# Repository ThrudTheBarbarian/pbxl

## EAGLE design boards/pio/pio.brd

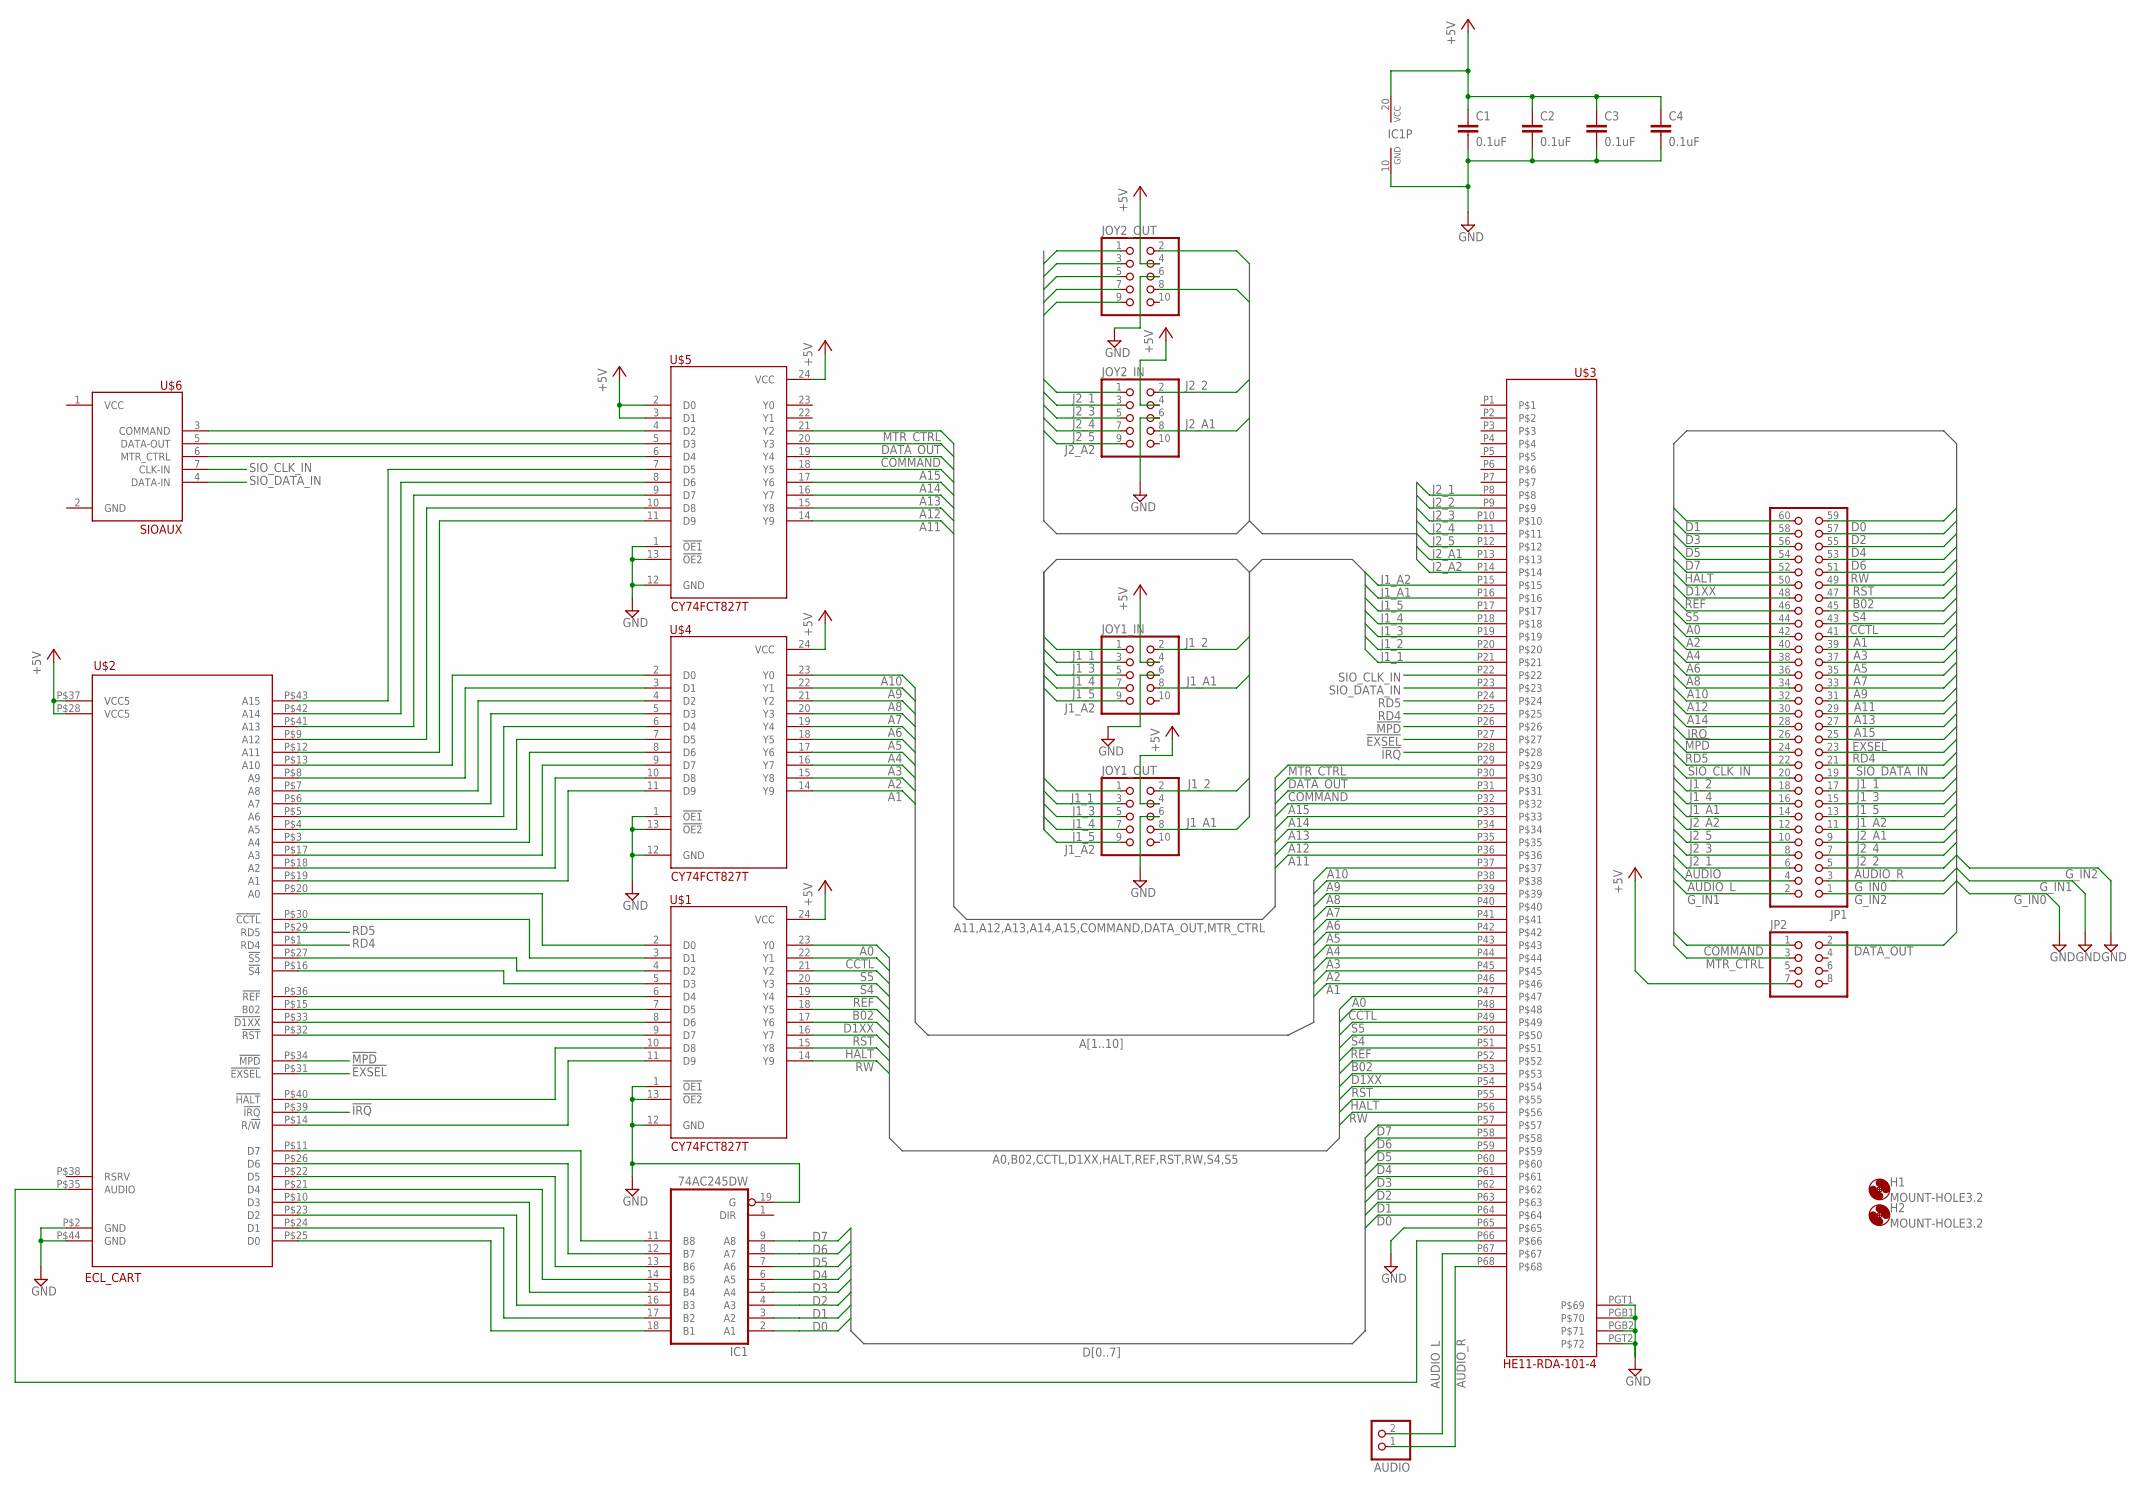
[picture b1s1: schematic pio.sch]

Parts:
AUDIO: PINHD-1X2; 1X02
C1, C2, C3, C4: 0.1uF; C1206
H1, H2: MOUNT-HOLE3.2; 3,2
IC1: 74AC245DW; SO20W
JOY1_IN, JOY1_OUT, JOY2_IN, JOY2_OUT: PINHD-2X5; 2X05
JP1: PINHD-2X30; 2X30
JP2: PINHD-2X4; 2X04
U$1, U$4, U$5: CY74FCT827T; SO24L
U$2: ECL_CART
U$3: HE11-RDA-101-4
U$6: SIOAUX; 1X07

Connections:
!EXSEL!: JP1.25, U$2.P$31 (!EXSEL!), U$3.P27
!IRQ!: JP1.28, U$2.P$39 (!IRQ!), U$3.P28
!MPD!: JP1.26, U$2.P$34 (!MPD!), U$3.P26
+5V: C1.1, C2.1, C3.1, C4.1, IC1.20 (VCC), JOY1_IN.4, JOY1_OUT.4, JOY2_IN.4, JOY2_OUT.4, JP2.7, U$1.24 (VCC), U$2.P$28 (VCC5), U$2.P$37 (VCC5), U$4.24 (VCC), U$5.2 (D0), U$5.3 (D1), U$5.24 (VCC)
A0: JP1.44, U$1.23 (Y0), U$3.P47
A1: JP1.41, U$3.P46, U$4.14 (Y9)
A2: JP1.42, U$3.P45, U$4.15 (Y8)
A3: JP1.39, U$3.P44, U$4.16 (Y7)
A4: JP1.40, U$3.P43, U$4.17 (Y6)
A5: JP1.37, U$3.P42, U$4.18 (Y5)
A6: JP1.38, U$3.P41, U$4.19 (Y4)
A7: JP1.35, U$3.P40, U$4.20 (Y3)
A8: JP1.36, U$3.P39, U$4.21 (Y2)
A9: JP1.33, U$3.P38, U$4.22 (Y1)
A10: JP1.34, U$3.P37, U$4.23 (Y0)
A11: JP1.31, U$3.P36, U$5.14 (Y9)
A12: JP1.32, U$3.P35, U$5.15 (Y8)
A13: JP1.29, U$3.P34, U$5.16 (Y7)
A14: JP1.30, U$3.P33, U$5.17 (Y6)
A15: JP1.27, U$3.P32, U$5.18 (Y5)
AUDIO: JP1.6, U$2.P$35 (AUDIO), U$3.P66
AUDIO_L: AUDIO.2, JP1.4, U$3.P67
AUDIO_R: AUDIO.1, JP1.5, U$3.P68
B02: JP1.47, U$1.18 (Y5), U$3.P52
CCTL: JP1.43, U$1.22 (Y1), U$3.P48
COMMAND: JP2.1, U$3.P31, U$5.19 (Y4)
D0: IC1.2 (A1), JP1.59, U$3.P64
D1: IC1.3 (A2), JP1.60, U$3.P63
D1XX: JP1.50, U$1.17 (Y6), U$3.P53
D2: IC1.4 (A3), JP1.57, U$3.P62
D3: IC1.5 (A4), JP1.58, U$3.P61
D4: IC1.6 (A5), JP1.55, U$3.P60
D5: IC1.7 (A6), JP1.56, U$3.P59
D6: IC1.8 (A7), JP1.53, U$3.P58
D7: IC1.9 (A8), JP1.54, U$3.P57
DATA_OUT: JP2.2, U$3.P30, U$5.20 (Y3)
GND: C1.2, C2.2, C3.2, C4.2, IC1.10 (GND), IC1.19 (G), JOY1_IN.6, JOY1_OUT.6, JOY2_IN.6, JOY2_OUT.6, U$1.1 (!OE1!), U$1.12 (GND), U$1.13 (!OE2!), U$2.P$2 (GND), U$2.P$44 (GND), U$3.P65, U$3.PGB1, U$3.PGB2, U$3.PGT1, U$3.PGT2, U$4.1 (!OE1!), U$4.12 (GND), U$4.13 (!OE2!), U$5.1 (!OE1!), U$5.12 (GND), U$5.13 (!OE2!)
G_IN0: JP1.3
G_IN1: JP1.2
G_IN2: JP1.1
HALT: JP1.52, U$1.15 (Y8), U$3.P55
J1_1: JOY1_IN.1, JOY1_OUT.1, JP1.19, U$3.P21
J1_2: JOY1_IN.2, JOY1_OUT.2, JP1.20, U$3.P20
J1_3: JOY1_IN.3, JOY1_OUT.3, JP1.17, U$3.P19
J1_4: JOY1_IN.5, JOY1_OUT.5, JP1.18, U$3.P18
J1_5: JOY1_IN.7, JOY1_OUT.7, JP1.15, U$3.P17
J1_A1: JOY1_IN.8, JOY1_OUT.8, JP1.16, U$3.P16
J1_A2: JOY1_IN.9, JOY1_OUT.9, JP1.13, U$3.P15
J2_1: JOY2_IN.1, JOY2_OUT.1, JP1.8, U$3.P8
J2_2: JOY2_IN.2, JOY2_OUT.2, JP1.7, U$3.P9
J2_3: JOY2_IN.3, JOY2_OUT.3, JP1.10, U$3.P10
J2_4: JOY2_IN.5, JOY2_OUT.5, JP1.9, U$3.P11
J2_5: JOY2_IN.7, JOY2_OUT.7, JP1.12, U$3.P12
J2_A1: JOY2_IN.8, JOY2_OUT.8, JP1.11, U$3.P13
J2_A2: JOY2_IN.9, JOY2_OUT.9, JP1.14, U$3.P14
MTR_CTRL: JP2.3, U$3.P29, U$5.21 (Y2)
unnamed: U$1.11 (D9), U$2.P$14 (R/!W!)
unnamed: U$1.10 (D8), U$2.P$40 (!HALT!)
unnamed: U$1.9 (D7), U$2.P$32 (!RST!)
unnamed: U$1.8 (D6), U$2.P$33 (!D1XX!)
unnamed: U$1.7 (D5), U$2.P$15 (B02)
unnamed: U$1.6 (D4), U$2.P$36 (!REF!)
unnamed: U$1.5 (D3), U$2.P$16 (!S4!)
unnamed: U$1.4 (D2), U$2.P$27 (!S5!)
unnamed: U$1.3 (D1), U$2.P$30 (!CCTL!)
unnamed: U$1.2 (D0), U$2.P$20 (A0)
unnamed: U$2.P$19 (A1), U$4.11 (D9)
unnamed: U$2.P$18 (A2), U$4.10 (D8)
unnamed: U$2.P$17 (A3), U$4.9 (D7)
unnamed: U$2.P$3 (A4), U$4.8 (D6)
unnamed: U$2.P$4 (A5), U$4.7 (D5)
unnamed: U$2.P$5 (A6), U$4.6 (D4)
unnamed: U$2.P$6 (A7), U$4.5 (D3)
unnamed: U$2.P$7 (A8), U$4.4 (D2)
unnamed: U$2.P$8 (A9), U$4.3 (D1)
unnamed: U$2.P$13 (A10), U$4.2 (D0)
unnamed: U$5.6 (D4), U$6.6 (MTR_CTRL)
unnamed: U$5.5 (D3), U$6.5 (DATA-OUT)
unnamed: U$5.4 (D2), U$6.3 (COMMAND)
unnamed: U$2.P$12 (A11), U$5.11 (D9)
unnamed: U$2.P$9 (A12), U$5.10 (D8)
unnamed: U$2.P$41 (A13), U$5.9 (D7)
unnamed: U$2.P$42 (A14), U$5.8 (D6)
unnamed: U$2.P$43 (A15), U$5.7 (D5)
unnamed: IC1.11 (B8), U$2.P$11 (D7)
unnamed: IC1.12 (B7), U$2.P$26 (D6)
unnamed: IC1.13 (B6), U$2.P$22 (D5)
unnamed: IC1.14 (B5), U$2.P$21 (D4)
unnamed: IC1.15 (B4), U$2.P$10 (D3)
unnamed: IC1.16 (B3), U$2.P$23 (D2)
unnamed: IC1.17 (B2), U$2.P$24 (D1)
unnamed: IC1.18 (B1), U$2.P$25 (D0)
RD4: JP1.23, U$2.P$1 (RD4), U$3.P25
RD5: JP1.24, U$2.P$29 (RD5), U$3.P24
REF: JP1.48, U$1.19 (Y4), U$3.P51
RST: JP1.49, U$1.16 (Y7), U$3.P54
RW: JP1.51, U$1.14 (Y9), U$3.P56
S4: JP1.45, U$1.20 (Y3), U$3.P50
S5: JP1.46, U$1.21 (Y2), U$3.P49
SIO_CLK_IN: JP1.22, U$3.P22, U$6.7 (CLK-IN)
SIO_DATA_IN: JP1.21, U$3.P23, U$6.4 (DATA-IN)

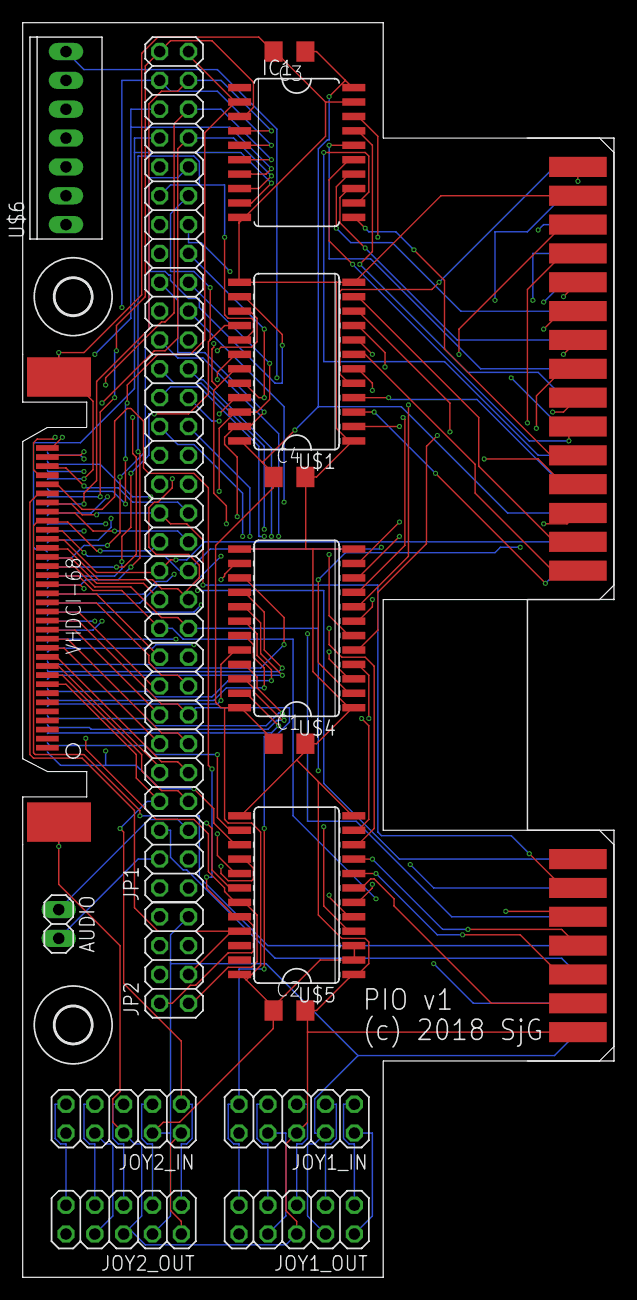
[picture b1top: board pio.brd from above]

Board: 4 copper layers, 52.1 x 110.5 mm, 20 parts (0 on the bottom side), 98 nets.

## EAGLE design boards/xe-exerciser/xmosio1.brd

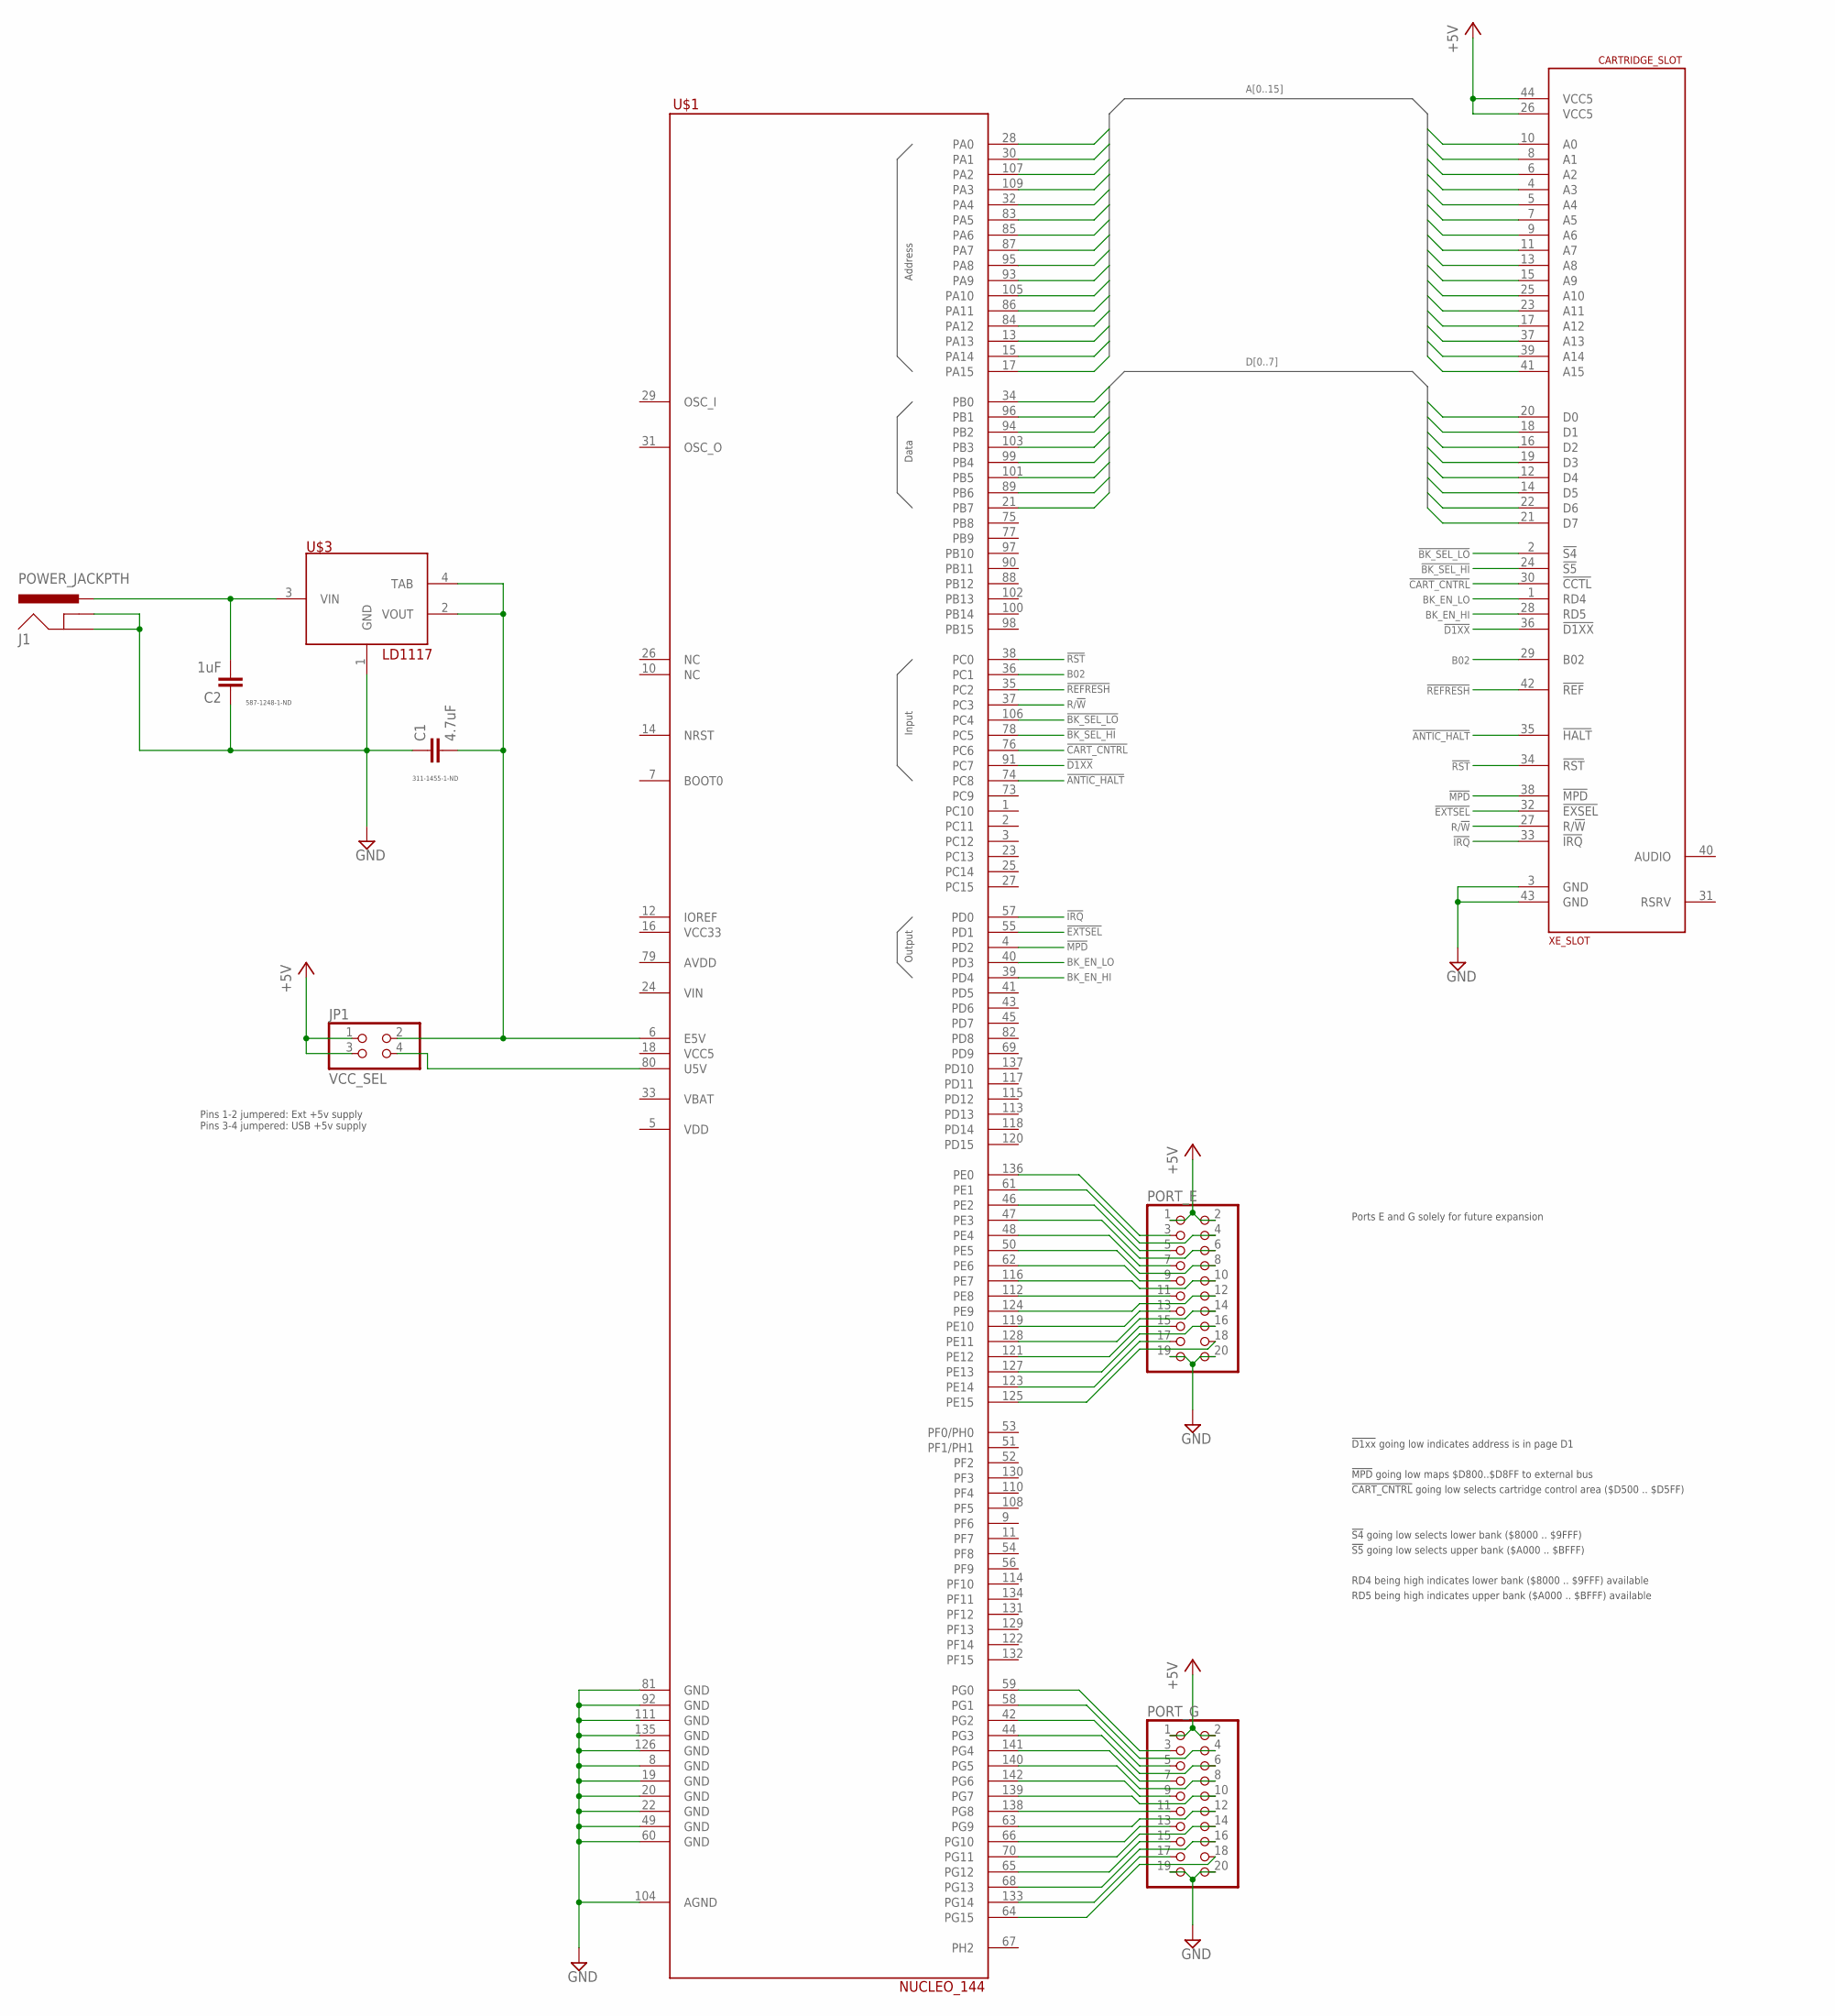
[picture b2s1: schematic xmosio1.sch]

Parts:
C1: 4.7uF; C0603
C2: 1uF; C0603
CARTRIDGE_SLOT: XE_SLOT
J1: POWER_JACKPTH; POWER_JACK_PTH
JP1: VCC_SEL; 2X02
PORT_E: PINHD-2X10; 2X10
PORT_G: PINHD-2X10; 2X10
U$1: NUCLEO_144
U$3: LD1117; SOT223

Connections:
!ANTIC_HALT!: CARTRIDGE_SLOT.35 (!HALT!), U$1.74 (PC8)
!BK_SEL_HI!: CARTRIDGE_SLOT.24 (!S5!), U$1.78 (PC5)
!BK_SEL_LO!: CARTRIDGE_SLOT.2 (!S4!), U$1.106 (PC4)
!CART_CNTRL!: CARTRIDGE_SLOT.30 (!CCTL!), U$1.76 (PC6)
!D1XX!: CARTRIDGE_SLOT.36 (!D1XX!), U$1.91 (PC7)
!EXTSEL!: CARTRIDGE_SLOT.32 (!EXSEL!), U$1.55 (PD1)
!IRQ!: CARTRIDGE_SLOT.33 (!IRQ!), U$1.57 (PD0)
!MPD!: CARTRIDGE_SLOT.38 (!MPD!), U$1.4 (PD2)
!REFRESH!: CARTRIDGE_SLOT.42 (!REF!), U$1.35 (PC2)
!RST!: CARTRIDGE_SLOT.34 (!RST!), U$1.38 (PC0)
+5V: CARTRIDGE_SLOT.26 (VCC5), CARTRIDGE_SLOT.44 (VCC5), JP1.1, JP1.3, PORT_E.1, PORT_E.2, PORT_G.1, PORT_G.2
A0: CARTRIDGE_SLOT.10 (A0), U$1.28 (PA0)
A1: CARTRIDGE_SLOT.8 (A1), U$1.30 (PA1)
A2: CARTRIDGE_SLOT.6 (A2), U$1.107 (PA2)
A3: CARTRIDGE_SLOT.4 (A3), U$1.109 (PA3)
A4: CARTRIDGE_SLOT.5 (A4), U$1.32 (PA4)
A5: CARTRIDGE_SLOT.7 (A5), U$1.83 (PA5)
A6: CARTRIDGE_SLOT.9 (A6), U$1.85 (PA6)
A7: CARTRIDGE_SLOT.11 (A7), U$1.87 (PA7)
A8: CARTRIDGE_SLOT.13 (A8), U$1.95 (PA8)
A9: CARTRIDGE_SLOT.15 (A9), U$1.93 (PA9)
A10: CARTRIDGE_SLOT.25 (A10), U$1.105 (PA10)
A11: CARTRIDGE_SLOT.23 (A11), U$1.86 (PA11)
A12: CARTRIDGE_SLOT.17 (A12), U$1.84 (PA12)
A13: CARTRIDGE_SLOT.37 (A13), U$1.13 (PA13)
A14: CARTRIDGE_SLOT.39 (A14), U$1.15 (PA14)
A15: CARTRIDGE_SLOT.41 (A15), U$1.17 (PA15)
B02: CARTRIDGE_SLOT.29 (B02), U$1.36 (PC1)
BK_EN_HI: CARTRIDGE_SLOT.28 (RD5), U$1.39 (PD4)
BK_EN_LO: CARTRIDGE_SLOT.1 (RD4), U$1.40 (PD3)
D0: CARTRIDGE_SLOT.20 (D0), U$1.34 (PB0)
D1: CARTRIDGE_SLOT.18 (D1), U$1.96 (PB1)
D2: CARTRIDGE_SLOT.16 (D2), U$1.94 (PB2)
D3: CARTRIDGE_SLOT.19 (D3), U$1.103 (PB3)
D4: CARTRIDGE_SLOT.12 (D4), U$1.99 (PB4)
D5: CARTRIDGE_SLOT.14 (D5), U$1.101 (PB5)
D6: CARTRIDGE_SLOT.22 (D6), U$1.89 (PB6)
D7: CARTRIDGE_SLOT.21 (D7), U$1.21 (PB7)
GND: C1.1, C2.1, CARTRIDGE_SLOT.3 (GND), CARTRIDGE_SLOT.43 (GND), J1.GND, J1.GNDBREAK, PORT_E.19, PORT_E.20, PORT_G.19, PORT_G.20, U$1.8 (GND), U$1.19 (GND), U$1.20 (GND), U$1.22 (GND), U$1.49 (GND), U$1.60 (GND), U$1.81 (GND), U$1.92 (GND), U$1.104 (AGND), U$1.111 (GND), U$1.126 (GND), U$1.135 (GND), U$3.1 (GND)
unnamed: C1.2, JP1.2, U$1.6 (E5V), U$3.2 (VOUT), U$3.4 (TAB)
unnamed: JP1.4, U$1.80 (U5V)
unnamed: PORT_E.3, U$1.136 (PE0)
unnamed: PORT_E.4, U$1.61 (PE1)
unnamed: PORT_E.5, U$1.46 (PE2)
unnamed: PORT_E.6, U$1.47 (PE3)
unnamed: PORT_E.7, U$1.48 (PE4)
unnamed: PORT_E.8, U$1.50 (PE5)
unnamed: PORT_E.9, U$1.62 (PE6)
unnamed: PORT_E.10, U$1.116 (PE7)
unnamed: PORT_E.11, U$1.112 (PE8)
unnamed: PORT_E.12, U$1.124 (PE9)
unnamed: PORT_E.13, U$1.119 (PE10)
unnamed: PORT_E.14, U$1.128 (PE11)
unnamed: PORT_E.15, U$1.121 (PE12)
unnamed: PORT_E.16, U$1.127 (PE13)
unnamed: PORT_E.17, U$1.123 (PE14)
unnamed: PORT_E.18, U$1.125 (PE15)
unnamed: PORT_G.3, U$1.59 (PG0)
unnamed: PORT_G.4, U$1.58 (PG1)
unnamed: PORT_G.5, U$1.42 (PG2)
unnamed: PORT_G.6, U$1.44 (PG3)
unnamed: PORT_G.7, U$1.141 (PG4)
unnamed: PORT_G.8, U$1.140 (PG5)
unnamed: PORT_G.9, U$1.142 (PG6)
unnamed: PORT_G.11, U$1.138 (PG8)
unnamed: C2.2, J1.PWR, U$3.3 (VIN)
unnamed: PORT_G.12, U$1.63 (PG9)
unnamed: PORT_G.13, U$1.66 (PG10)
unnamed: PORT_G.14, U$1.70 (PG11)
unnamed: PORT_G.15, U$1.65 (PG12)
unnamed: PORT_G.16, U$1.68 (PG13)
unnamed: PORT_G.17, U$1.133 (PG14)
unnamed: PORT_G.18, U$1.64 (PG15)
PORT_G: PORT_G.10, U$1.139 (PG7)
R/!W!: CARTRIDGE_SLOT.27 (R/!W!), U$1.37 (PC3)

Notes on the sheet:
!MPD! going low maps $D800..$D8FF to external bus
!S4! going low selects lower bank ($8000 .. $9FFF)
!S5! going low selects upper bank ($A000 .. $BFFF)
!CART_CNTRL! going low selects cartridge control area ($D500 .. $D5FF)
!D1xx! going low indicates address is in page D1
RD4 being high indicates lower bank ($8000 .. $9FFF) available
RD5 being high indicates upper bank ($A000 .. $BFFF) available
Output
Input
Data
Address
Pins 1-2 jumpered: Ext +5v supply Pins 3-4 jumpered: USB +5v supply
Ports E and G solely for future expansion
311-1455-1-ND
587-1248-1-ND

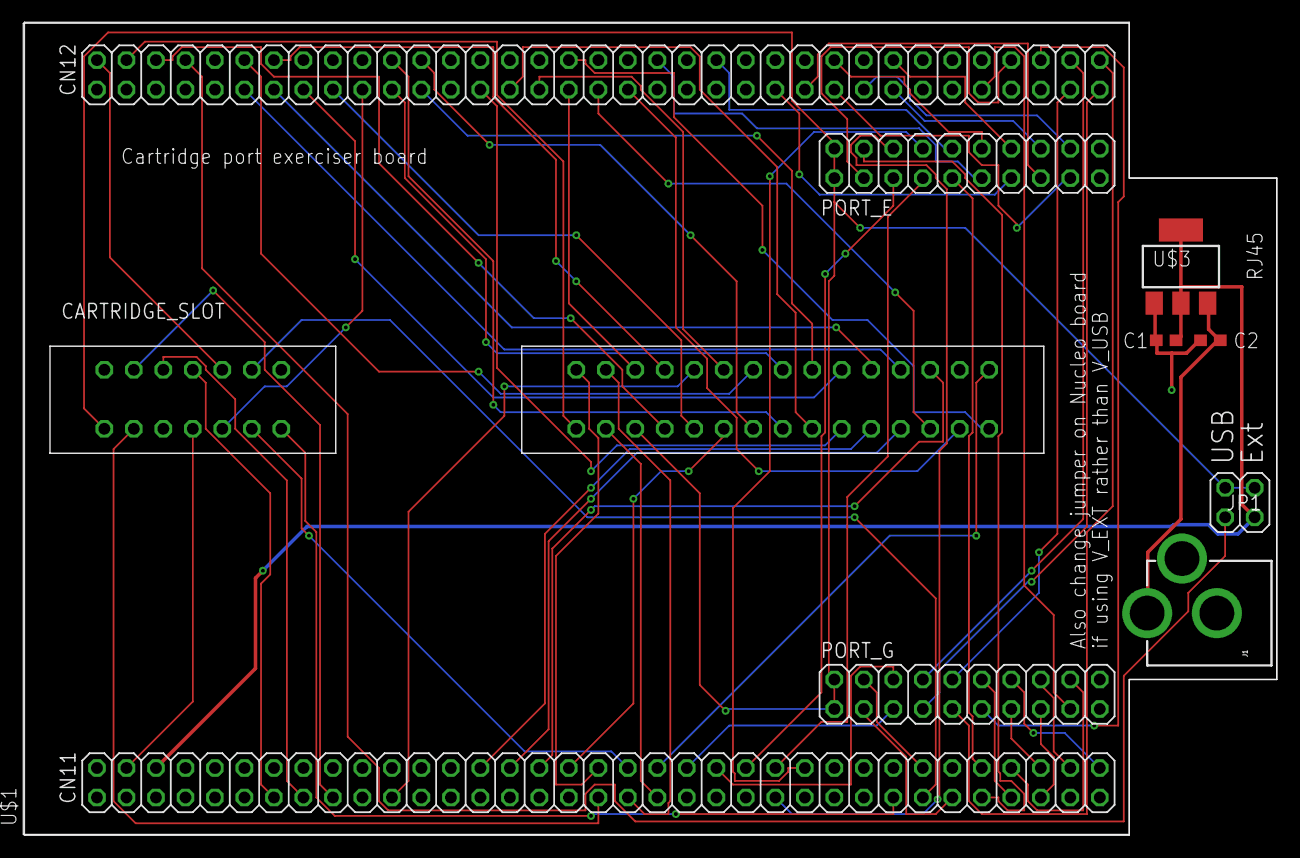
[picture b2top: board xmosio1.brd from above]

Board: 2 copper layers, 108.0 x 69.8 mm, 9 parts (0 on the bottom side), 75 nets.

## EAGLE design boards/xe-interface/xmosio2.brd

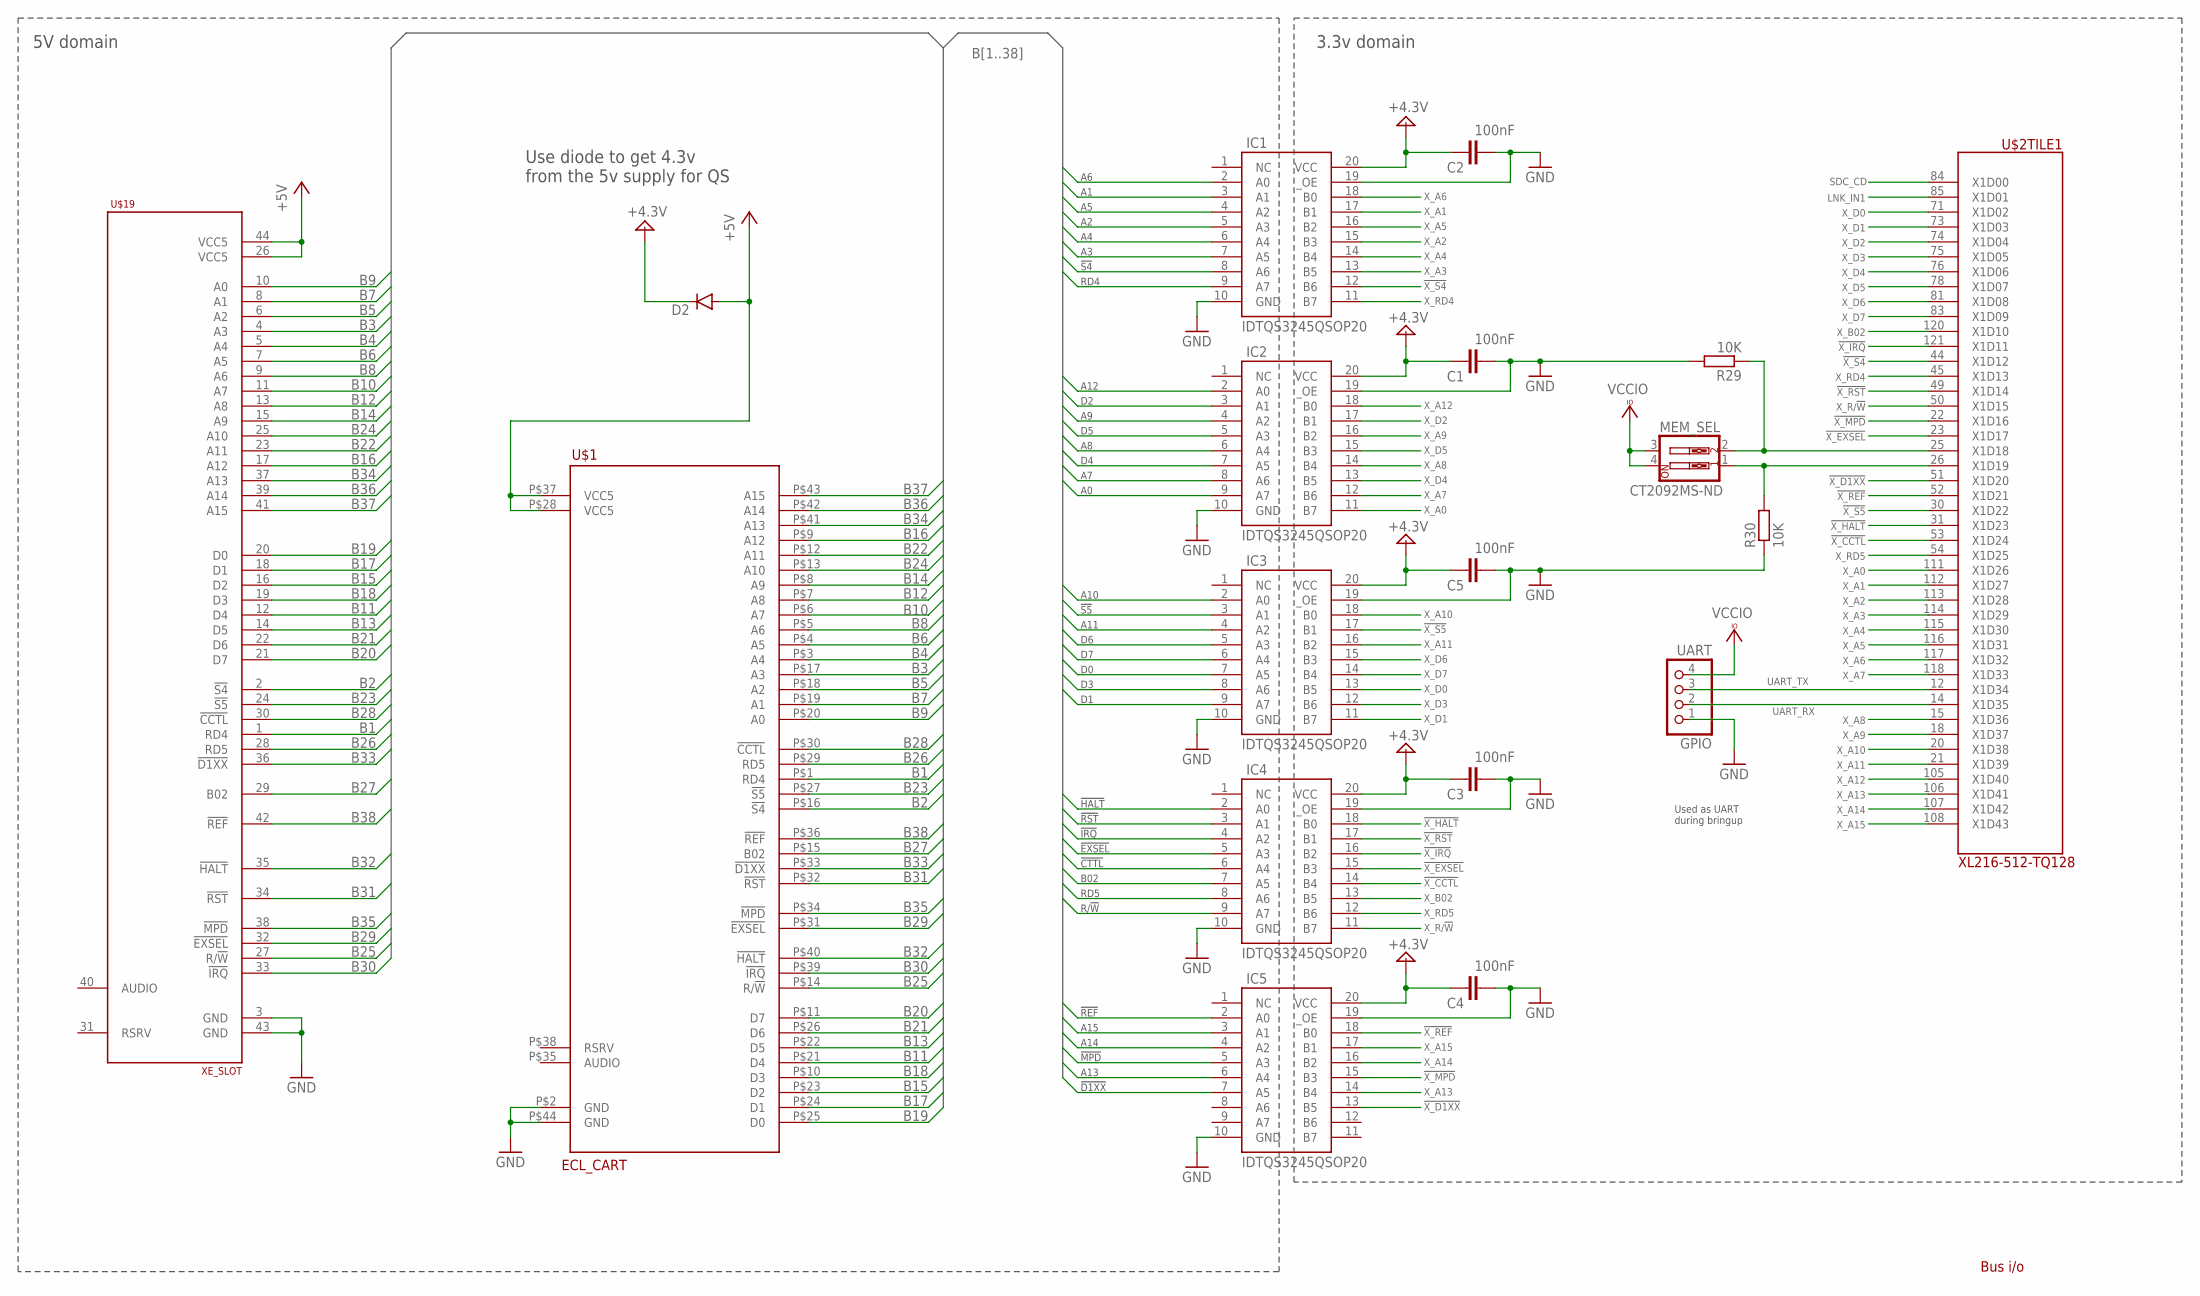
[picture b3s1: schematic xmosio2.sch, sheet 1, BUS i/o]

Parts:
C1, C2, C3, C4, C5: 100nF; C1206
D2: DIODE; DIODE-1N4001-KIT
GPIO: UART; 1X04
IC1, IC2, IC3, IC4, IC5: IDTQS3245QSOP20; QSOP20
MEM_SEL: CT2092MS-ND; EDG-02
R29, R30: 10K; R1206
U$1: ECL_CART
U$2: XL216-512-TQ128; TQFP128
U$19: XE_SLOT

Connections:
!X_CCTL!: IC4.14 (B4), U$2.53 (X1D24)
!X_D1XX!: IC5.13 (B5), U$2.51 (X1D20)
!X_EXSEL!: IC4.15 (B3), U$2.23 (X1D17)
!X_HALT!: IC4.18 (B0), U$2.31 (X1D23)
!X_IRQ!: IC4.16 (B2), U$2.121 (X1D11)
!X_MPD!: IC5.15 (B3), U$2.22 (X1D16)
!X_REF!: IC5.18 (B0), U$2.52 (X1D21)
!X_RST!: IC4.17 (B1), U$2.49 (X1D14)
!X_S4!: IC1.12 (B6), U$2.44 (X1D12)
!X_S5!: IC3.17 (B1), U$2.30 (X1D22)
+4.3V: C1.1, C2.1, C3.1, C4.1, C5.1, D2.C, IC1.20 (VCC), IC2.20 (VCC), IC3.20 (VCC), IC4.20 (VCC), IC5.20 (VCC)
+5V: D2.A, U$1.P$28 (VCC5), U$1.P$37 (VCC5), U$19.26 (VCC5), U$19.44 (VCC5); also elsewhere on the board
B1: IC1.9 (A7), U$1.P$1 (RD4), U$19.1 (RD4)
B2: IC1.8 (A6), U$1.P$16 (!S4!), U$19.2 (!S4!)
B3: IC1.7 (A5), U$1.P$17 (A3), U$19.4 (A3)
B4: IC1.6 (A4), U$1.P$3 (A4), U$19.5 (A4)
B5: IC1.5 (A3), U$1.P$18 (A2), U$19.6 (A2)
B6: IC1.4 (A2), U$1.P$4 (A5), U$19.7 (A5)
B7: IC1.3 (A1), U$1.P$19 (A1), U$19.8 (A1)
B8: IC1.2 (A0), U$1.P$5 (A6), U$19.9 (A6)
B9: IC2.9 (A7), U$1.P$20 (A0), U$19.10 (A0)
B10: IC2.8 (A6), U$1.P$6 (A7), U$19.11 (A7)
B11: IC2.7 (A5), U$1.P$21 (D4), U$19.12 (D4)
B12: IC2.6 (A4), U$1.P$7 (A8), U$19.13 (A8)
B13: IC2.5 (A3), U$1.P$22 (D5), U$19.14 (D5)
B14: IC2.4 (A2), U$1.P$8 (A9), U$19.15 (A9)
B15: IC2.3 (A1), U$1.P$23 (D2), U$19.16 (D2)
B16: IC2.2 (A0), U$1.P$9 (A12), U$19.17 (A12)
B17: IC3.9 (A7), U$1.P$24 (D1), U$19.18 (D1)
B18: IC3.8 (A6), U$1.P$10 (D3), U$19.19 (D3)
B19: IC3.7 (A5), U$1.P$25 (D0), U$19.20 (D0)
B20: IC3.6 (A4), U$1.P$11 (D7), U$19.21 (D7)
B21: IC3.5 (A3), U$1.P$26 (D6), U$19.22 (D6)
B22: IC3.4 (A2), U$1.P$12 (A11), U$19.23 (A11)
B23: IC3.3 (A1), U$1.P$27 (!S5!), U$19.24 (!S5!)
B24: IC3.2 (A0), U$1.P$13 (A10), U$19.25 (A10)
B25: IC4.9 (A7), U$1.P$14 (R/!W!), U$19.27 (R/!W!)
B26: IC4.8 (A6), U$1.P$29 (RD5), U$19.28 (RD5)
B27: IC4.7 (A5), U$1.P$15 (B02), U$19.29 (B02)
B28: IC4.6 (A4), U$1.P$30 (!CCTL!), U$19.30 (!CCTL!)
B29: IC4.5 (A3), U$1.P$31 (!EXSEL!), U$19.32 (!EXSEL!)
B30: IC4.4 (A2), U$1.P$39 (!IRQ!), U$19.33 (!IRQ!)
B31: IC4.3 (A1), U$1.P$32 (!RST!), U$19.34 (!RST!)
B32: IC4.2 (A0), U$1.P$40 (!HALT!), U$19.35 (!HALT!)
B33: IC5.7 (A5), U$1.P$33 (!D1XX!), U$19.36 (!D1XX!)
B34: IC5.6 (A4), U$1.P$41 (A13), U$19.37 (A13)
B35: IC5.5 (A3), U$1.P$34 (!MPD!), U$19.38 (!MPD!)
B36: IC5.4 (A2), U$1.P$42 (A14), U$19.39 (A14)
B37: IC5.3 (A1), U$1.P$43 (A15), U$19.41 (A15)
B38: IC5.2 (A0), U$1.P$36 (!REF!), U$19.42 (!REF!)
GND: C1.2, C2.2, C3.2, C4.2, C5.2, GPIO.1, IC1.10 (GND), IC1.19 (_OE), IC2.10 (GND), IC2.19 (_OE), IC3.10 (GND), IC3.19 (_OE), IC4.10 (GND), IC4.19 (_OE), IC5.10 (GND), IC5.19 (_OE), R29.2, R30.1, U$1.P$2 (GND), U$1.P$44 (GND), U$19.3 (GND), U$19.43 (GND); also elsewhere on the board
LNK_IN1: U$2.85 (X1D01); also elsewhere on the board
unnamed: MEM_SEL.2, R29.1, U$2.25 (X1D18)
unnamed: MEM_SEL.1, R30.2, U$2.26 (X1D19)
SDC_CD: U$2.84 (X1D00); also elsewhere on the board
UART_RX: GPIO.2, U$2.14 (X1D35); also elsewhere on the board
UART_TX: GPIO.3, U$2.12 (X1D34); also elsewhere on the board
VCCIO: GPIO.4, MEM_SEL.3, MEM_SEL.4; also elsewhere on the board
X_A0: IC2.11 (B7), U$2.111 (X1D26)
X_A1: IC1.17 (B1), U$2.112 (X1D27)
X_A2: IC1.15 (B3), U$2.113 (X1D28)
X_A3: IC1.13 (B5), U$2.114 (X1D29)
X_A4: IC1.14 (B4), U$2.115 (X1D30)
X_A5: IC1.16 (B2), U$2.116 (X1D31)
X_A6: IC1.18 (B0), U$2.117 (X1D32)
X_A7: IC2.12 (B6), U$2.118 (X1D33)
X_A8: IC2.14 (B4), U$2.15 (X1D36)
X_A9: IC2.16 (B2), U$2.18 (X1D37)
X_A10: IC3.18 (B0), U$2.20 (X1D38)
X_A11: IC3.16 (B2), U$2.21 (X1D39)
X_A12: IC2.18 (B0), U$2.105 (X1D40)
X_A13: IC5.14 (B4), U$2.106 (X1D41)
X_A14: IC5.16 (B2), U$2.107 (X1D42)
X_A15: IC5.17 (B1), U$2.108 (X1D43)
X_B02: IC4.13 (B5), U$2.120 (X1D10)
X_D0: IC3.13 (B5), U$2.71 (X1D02)
X_D1: IC3.11 (B7), U$2.73 (X1D03)
X_D2: IC2.17 (B1), U$2.74 (X1D04)
X_D3: IC3.12 (B6), U$2.75 (X1D05)
X_D4: IC2.13 (B5), U$2.76 (X1D06)
X_D5: IC2.15 (B3), U$2.78 (X1D07)
X_D6: IC3.15 (B3), U$2.81 (X1D08)
X_D7: IC3.14 (B4), U$2.83 (X1D09)
X_R/!W!: IC4.11 (B7), U$2.50 (X1D15)
X_RD4: IC1.11 (B7), U$2.45 (X1D13)
X_RD5: IC4.12 (B6), U$2.54 (X1D25)

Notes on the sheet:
A15
A14
A13
A12
A11
A10
!CTTL!
B02
RD5
RD4
!S5!
!S4!
!REF!
!D1XX!
!RST!
!MPD!
!EXSEL!
!HALT!
!IRQ!
R/!W!
Bus i/o
5V domain
3.3v domain
Use diode to get 4.3v from the 5v supply for QS
Used as UART during bringup

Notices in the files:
boards/pio/pio.brd:
(c) 2018 SjG
parts and their libraries:
SparkFun-Connectors: Licensing: Creative Commons ShareAlike 4.0 International - https://creativecommons.org/licenses/by-sa/4.0
SparkFun: Licensing: CC v3.0 Share-Alike You are welcome to use this library for commercial purposes.
InputOutputIO: Copyright: Würth Elektronik
